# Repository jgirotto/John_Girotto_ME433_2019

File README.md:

# John_Girotto_ME433_2019
ME433 Assignment Submission and Version Tracking

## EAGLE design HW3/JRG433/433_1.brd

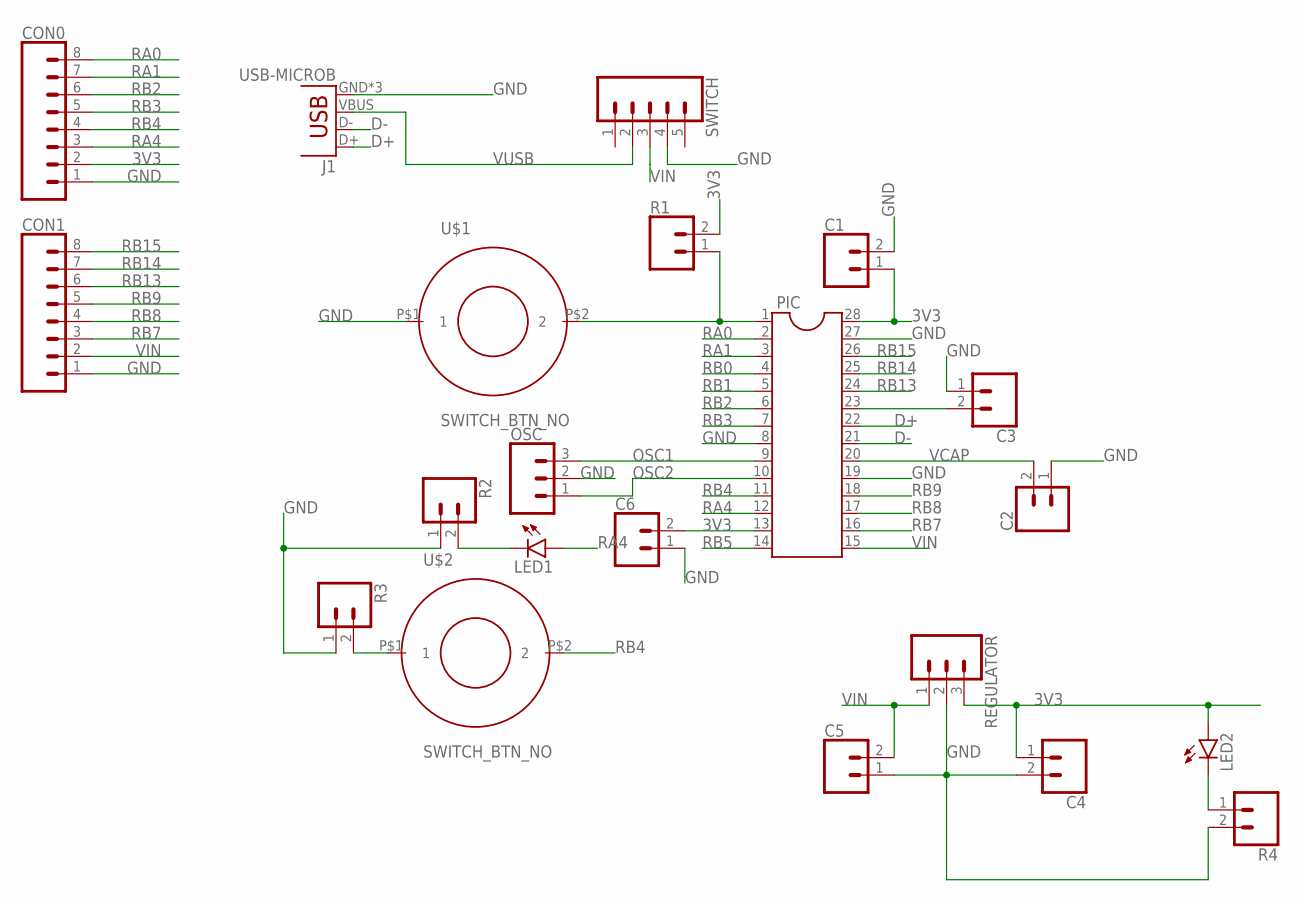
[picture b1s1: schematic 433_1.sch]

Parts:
C1, C2, C3, C4, C5, C6: CONN_02; 1X02
CON0, CON1: CONN_08"; 1X08
J1: USB-MICROB
LED1, LED2: LED3MM
OSC: CONN_03; 1X03
PIC: DIL28-4
R1, R2, R3, R4: CONN_02; 1X02
REGULATOR: CONN_03; 1X03
SWITCH: CONN_05; 1X05
U$1, U$2: SWITCH_BTN_NO; BTN_2

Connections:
3V3: C1.1, C3.2, C4.1, C6.2, CON0.2, LED2.A, PIC.13, PIC.23, PIC.28, R1.2, REGULATOR.3
D+: J1.D+, PIC.22
D-: J1.D-, PIC.21
GND: C1.2, C2.1, C3.1, C4.2, C5.1, C6.1, CON0.1, CON1.1, J1.GND, J1.MT1 (GND), J1.MT2 (GND), OSC.2, PIC.8, PIC.19, PIC.27, R2.1, R3.1, R4.2, REGULATOR.2, SWITCH.4, U$1.P$1 (1)
unnamed: LED1.K (C), R2.2
unnamed: R3.2, U$2.P$1 (1)
unnamed: LED2.K (C), R4.1
unnamed: PIC.1, R1.1, U$1.P$2 (2)
OSC1: OSC.3, PIC.9
OSC2: OSC.1, PIC.10
RA0: CON0.8, PIC.2
RA1: CON0.7, PIC.3
RA4: CON0.3, LED1.A, PIC.12
RB0: PIC.4
RB1: PIC.5
RB2: CON0.6, PIC.6
RB3: CON0.5, PIC.7
RB4: CON0.4, PIC.11, U$2.P$2 (2)
RB5: PIC.14
RB7: CON1.3, PIC.16
RB8: CON1.4, PIC.17
RB9: CON1.5, PIC.18
RB13: CON1.6, PIC.24
RB14: CON1.7, PIC.25
RB15: CON1.8, PIC.26
VCAP: C2.2, PIC.20
VIN: C5.2, CON1.2, PIC.15, REGULATOR.1, SWITCH.3
VUSB: J1.VBUS, SWITCH.2

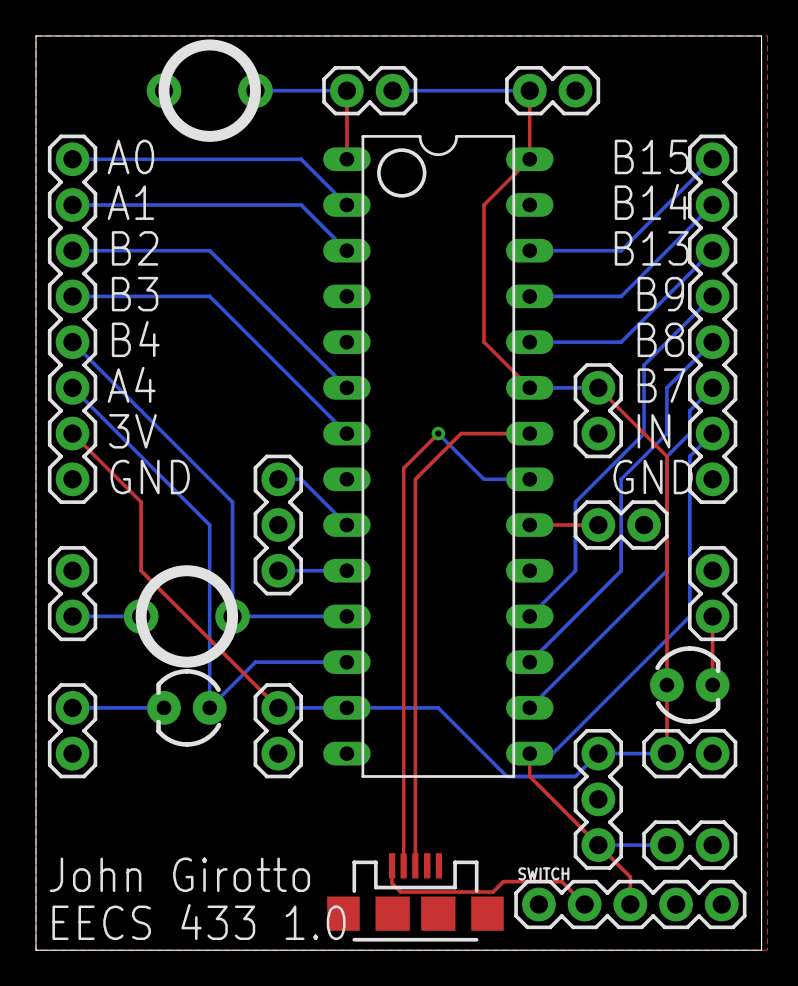
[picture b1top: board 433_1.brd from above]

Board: 2 copper layers, 40.3 x 50.8 mm, 21 parts (0 on the bottom side), 25 nets.

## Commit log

2019-04-12 Upload Board and Schematic 1.0

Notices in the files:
parts and their libraries:
SparkFun-Connectors: Licensing: Creative Commons ShareAlike 4.0 International - https://creativecommons.org/licenses/by-sa/4.0
